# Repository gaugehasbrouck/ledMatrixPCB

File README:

Project start date: 3/2025
The goal of this project is to learn PCB design using KiCad. 
The specfic goal of this project is to build a PCB that plugs into a USB port and using the power lines from the USB device, it will power a ATtiny84 that controls two shift registers which controls the 8x8 led matrix. 

Please check out the images/ for schematic images and pcb 3d layout images. :)

I would like to create a library for various different animations. And eventually even be able to install custom libraries for custom animations for friends and family. 

If you would like to talk about this project, maybe give some advice or ask questions, feel free to send me an email at gaugehasbrouck@gmail.com

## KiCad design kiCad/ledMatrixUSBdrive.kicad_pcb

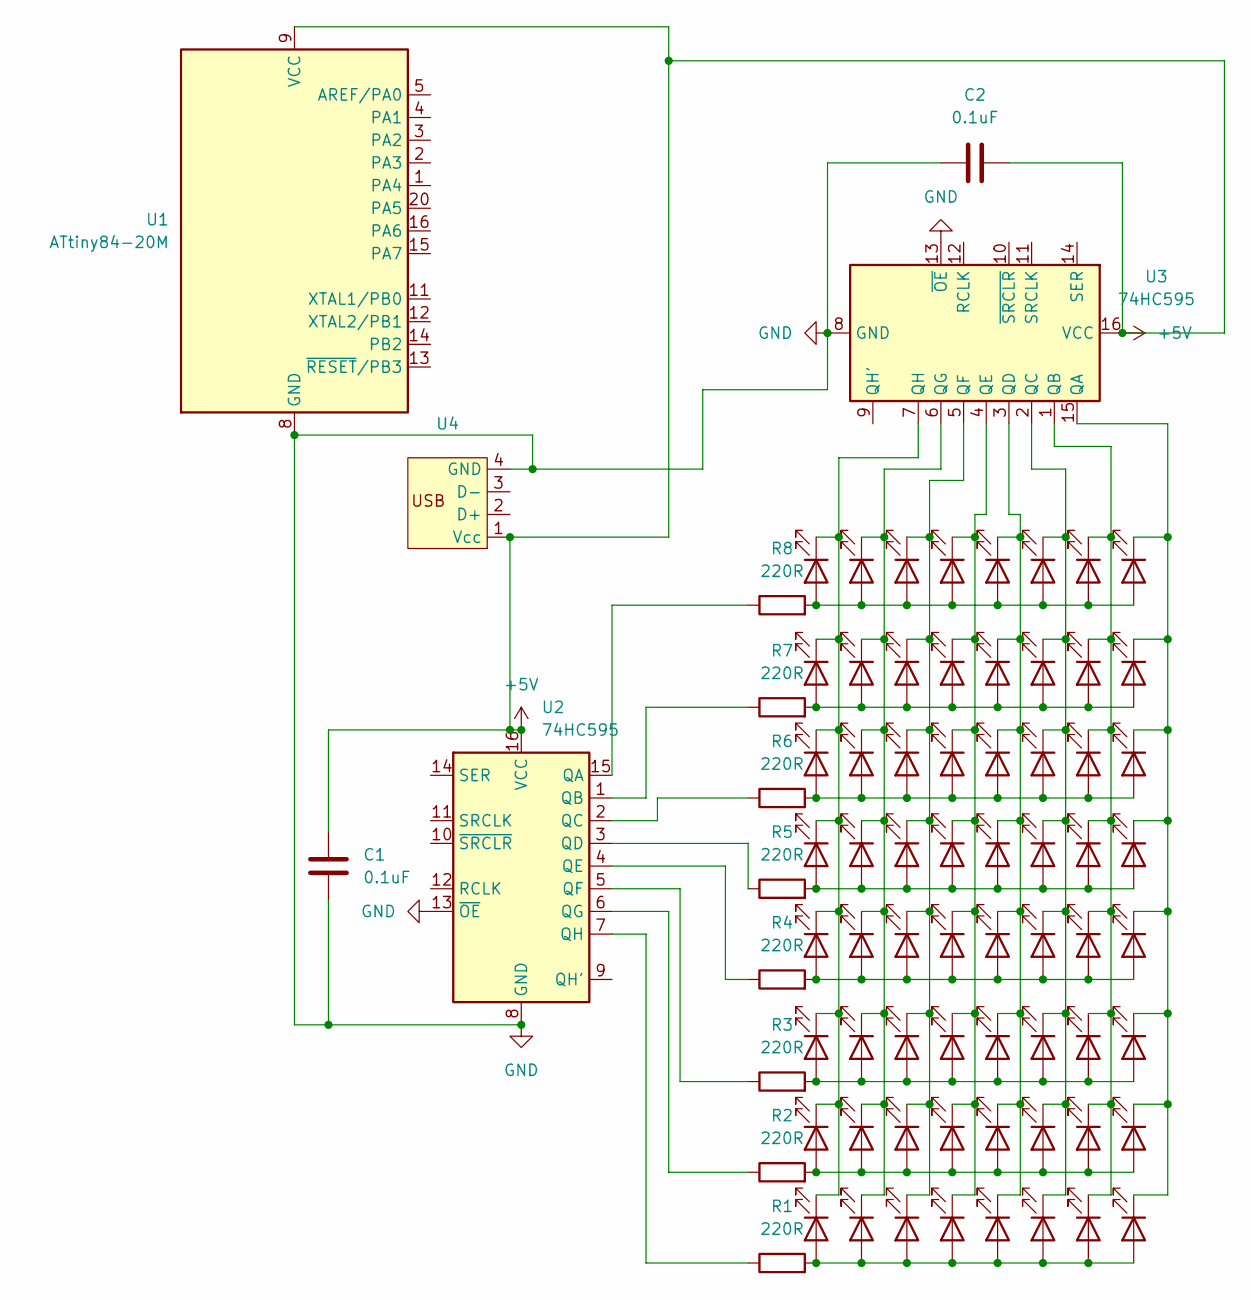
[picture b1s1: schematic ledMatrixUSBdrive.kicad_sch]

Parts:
C1, C2: 0.1uF; C_1206_3216Metric
D1, D2, D3, D4, D5, D6, D7, D8, D9, D10, D11, D12, D13, D14, D15, D16, D17, D18, D19, D20, D21, D22, D23, D24, D25, D26, D27, D28, D29, D30, D31, D32, D33, D34, D35, D36, D37, D38, D39, D40, D41, D42, D43, D44, D45, D46, D47, D48, D49, D50, D51, D52, D53, D54, D55, D56, D57, D58, D59, D60, D61, D62, D63, D64: LED; LED_1206_3216Metric
R1, R2, R3, R4, R5, R6, R7, R8: 220R; R_1206_3216Metric
U1: ATtiny84-20M; QFN-20-1EP_4x4mm_P0.5mm_EP2.6x2.6mm
U2, U3: 74HC595; SOIC-16_3.9x9.9mm_P1.27mm
U4: PSB_USB_CONN

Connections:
+5V: C1.1, C2.2, U1.9 (VCC), U2.16 (VCC), U3.16 (VCC), U4.1 (Vcc)
GND: C1.2, C2.1, U1.8 (GND), U1.21 (GND), U2.8 (GND), U2.13 (~OE), U3.8 (GND), U3.13 (~OE), U4.4 (GND)
unnamed: D1.2 (A), D2.2 (A), D3.2 (A), D4.2 (A), D5.2 (A), D6.2 (A), D7.2 (A), D8.2 (A), R8.2
unnamed: D1.1 (K), D9.1 (K), D17.1 (K), D25.1 (K), D33.1 (K), D41.1 (K), D49.1 (K), D57.1 (K), U3.7 (QH)
unnamed: D9.2 (A), D10.2 (A), D11.2 (A), D12.2 (A), D13.2 (A), D14.2 (A), D15.2 (A), D16.2 (A), R7.2
unnamed: D2.1 (K), D10.1 (K), D18.1 (K), D26.1 (K), D34.1 (K), D42.1 (K), D50.1 (K), D58.1 (K), U3.6 (QG)
unnamed: D3.1 (K), D11.1 (K), D19.1 (K), D27.1 (K), D35.1 (K), D43.1 (K), D51.1 (K), D59.1 (K), U3.5 (QF)
unnamed: D4.1 (K), D12.1 (K), D20.1 (K), D28.1 (K), D36.1 (K), D44.1 (K), D52.1 (K), D60.1 (K), U3.4 (QE)
unnamed: D5.1 (K), D13.1 (K), D21.1 (K), D29.1 (K), D37.1 (K), D45.1 (K), D53.1 (K), D61.1 (K), U3.3 (QD)
unnamed: D6.1 (K), D14.1 (K), D22.1 (K), D30.1 (K), D38.1 (K), D46.1 (K), D54.1 (K), D62.1 (K), U3.2 (QC)
unnamed: D7.1 (K), D15.1 (K), D23.1 (K), D31.1 (K), D39.1 (K), D47.1 (K), D55.1 (K), D63.1 (K), U3.1 (QB)
unnamed: D8.1 (K), D16.1 (K), D24.1 (K), D32.1 (K), D40.1 (K), D48.1 (K), D56.1 (K), D64.1 (K), U3.15 (QA)
unnamed: D17.2 (A), D18.2 (A), D19.2 (A), D20.2 (A), D21.2 (A), D22.2 (A), D23.2 (A), D24.2 (A), R6.2
unnamed: D25.2 (A), D26.2 (A), D27.2 (A), D28.2 (A), D29.2 (A), D30.2 (A), D31.2 (A), D32.2 (A), R5.2
unnamed: D33.2 (A), D34.2 (A), D35.2 (A), D36.2 (A), D37.2 (A), D38.2 (A), D39.2 (A), D40.2 (A), R4.2
unnamed: D41.2 (A), D42.2 (A), D43.2 (A), D44.2 (A), D45.2 (A), D46.2 (A), D47.2 (A), D48.2 (A), R3.2
unnamed: D49.2 (A), D50.2 (A), D51.2 (A), D52.2 (A), D53.2 (A), D54.2 (A), D55.2 (A), D56.2 (A), R2.2
unnamed: D57.2 (A), D58.2 (A), D59.2 (A), D60.2 (A), D61.2 (A), D62.2 (A), D63.2 (A), D64.2 (A), R1.2
unnamed: R8.1, U2.15 (QA)
unnamed: R7.1, U2.1 (QB)
unnamed: R6.1, U2.2 (QC)
unnamed: R5.1, U2.3 (QD)
unnamed: R4.1, U2.4 (QE)
unnamed: R3.1, U2.5 (QF)
unnamed: R2.1, U2.6 (QG)
unnamed: R1.1, U2.7 (QH)

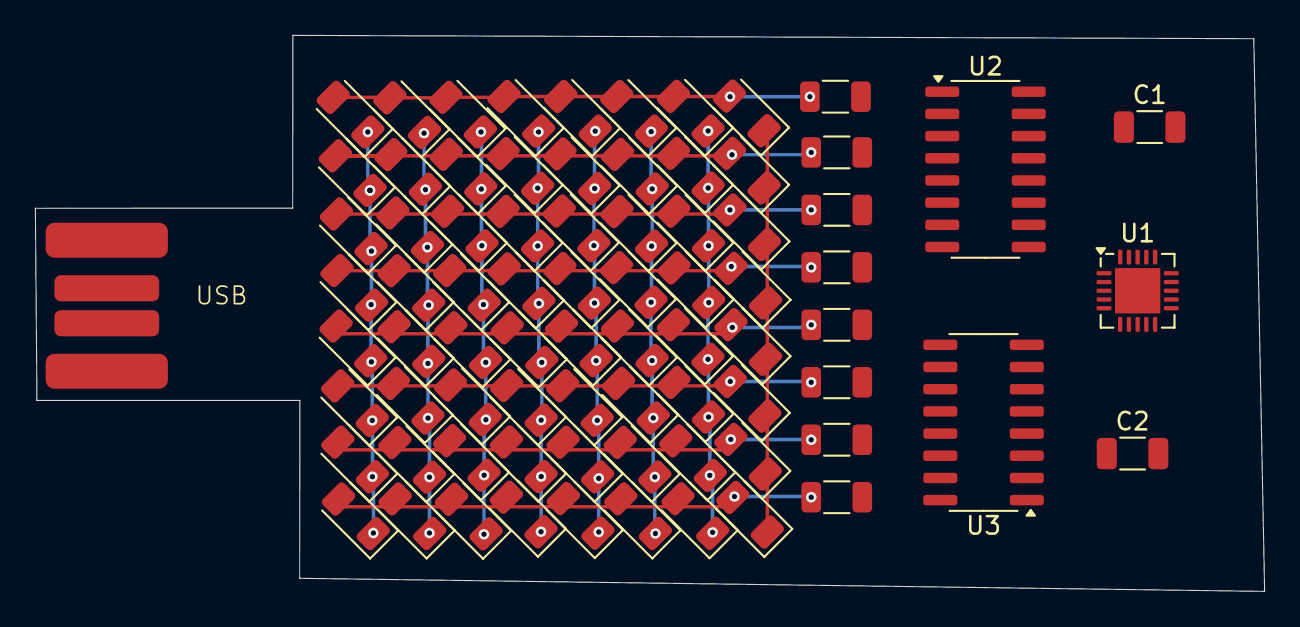
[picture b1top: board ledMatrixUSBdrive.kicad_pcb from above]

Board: 2 copper layers, 70.4 x 31.8 mm, 78 parts (0 on the bottom side), 26 nets.

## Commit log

2025-04-01 added kiCad project files
2025-04-02 added wokwi files
2025-04-02 added main.cpp
2025-04-02 added README
2025-04-02 added images folder as well as two images
2025-04-02 addded schematic layout image
